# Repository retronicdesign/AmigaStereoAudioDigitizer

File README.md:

# Amiga Stereo Audio Digitizer v1.3b
An Amiga Stereo Digitizer for Audio. Compatible with most softwares. Input gain is adjustable.

## Schematic

## Theory of Operation
This board can convert one or two audio channel to uncompressed digital 8-bit audio stream.  
It connects to the Amiga Parallel Port through a D-SUB-25 male connector. 
It was sucessfully tested with Audio Master IV at a maximum rate of 53KSPS (mono) on an unmodified Amiga 500.

Audio processing on the board is as follow:

1. Audio is preamplified to +5v p-p and biased at +2.5v
2. Left and right channels are multiplexed and sampled alternatively
3. Audio signal is converted to 8-bit using an high-speed ADC

Parallel port signals used to control the process are:
- /STROBE: Amiga ask for the next sample 
- /SELECT: Select the current channel for sample (0=Left, 1= Right)
## PCB

## Bill of materials
| Reference | Quantity | Value | Component | Description | Vendor |
| --- | --- | --- | --- | --- | --- |
| C1, C2, C3,  | 3 | 10uF 10v 10% | Electrolytic, Radial |
| C4, C5, C6,  | 3 | 100nF 50v 10% | Ceramic |
| C7,  | 1 | 47uF 10v 10% | Electrolytic, Radial |
| J1,  | 1 |  | SJ1-3525NG-PI | Stereo jack female connector, Red | Same Sky |
| J2,  | 1 |  | DB25-SL-24 | PCB D-SUB 25 male, Right-Angle | Adam Tech |
| R1, R2, R3, R4,  | 4 | 1K 1% 1/4 Watts | Resistor | Trough hole resistor |
| RV1,  | 1 | A10K | RK09K1110A0J |  Single right-angle potentiometer, 10K Exponential | ALPS |
| U1,  | 1 | | MCP6002 | 1MHz, Low-Power Op Amp, DIP-8 | Microchip |
| U2,  | 1 | | ADG419BNZ | Single SPDT CMOS Analog Switch, DIP-8 | Analog Devices |
| U3,  | 1 | | ADC0820CCN+ | Analog to Digital 8 bits converter, DIP-20 | National Semiconductors |
## Revision information
- 1.0 Original release
- 1.1 Modified D-Sub 25M connector footprint
- 1.2 Modified RCA connector footprint
- 1.3 Redesigned bias for more stable reference and simplified op-amp circuitry + PCB redesign
- 1.3a Corrected routing from v1.3 (issue#2) + replaced SPDT Analog Switch for new part
- 1.3b Corrected routing from v1.3a (issue#3) + replaced RCA plugs for Stereo jack 3.5mm

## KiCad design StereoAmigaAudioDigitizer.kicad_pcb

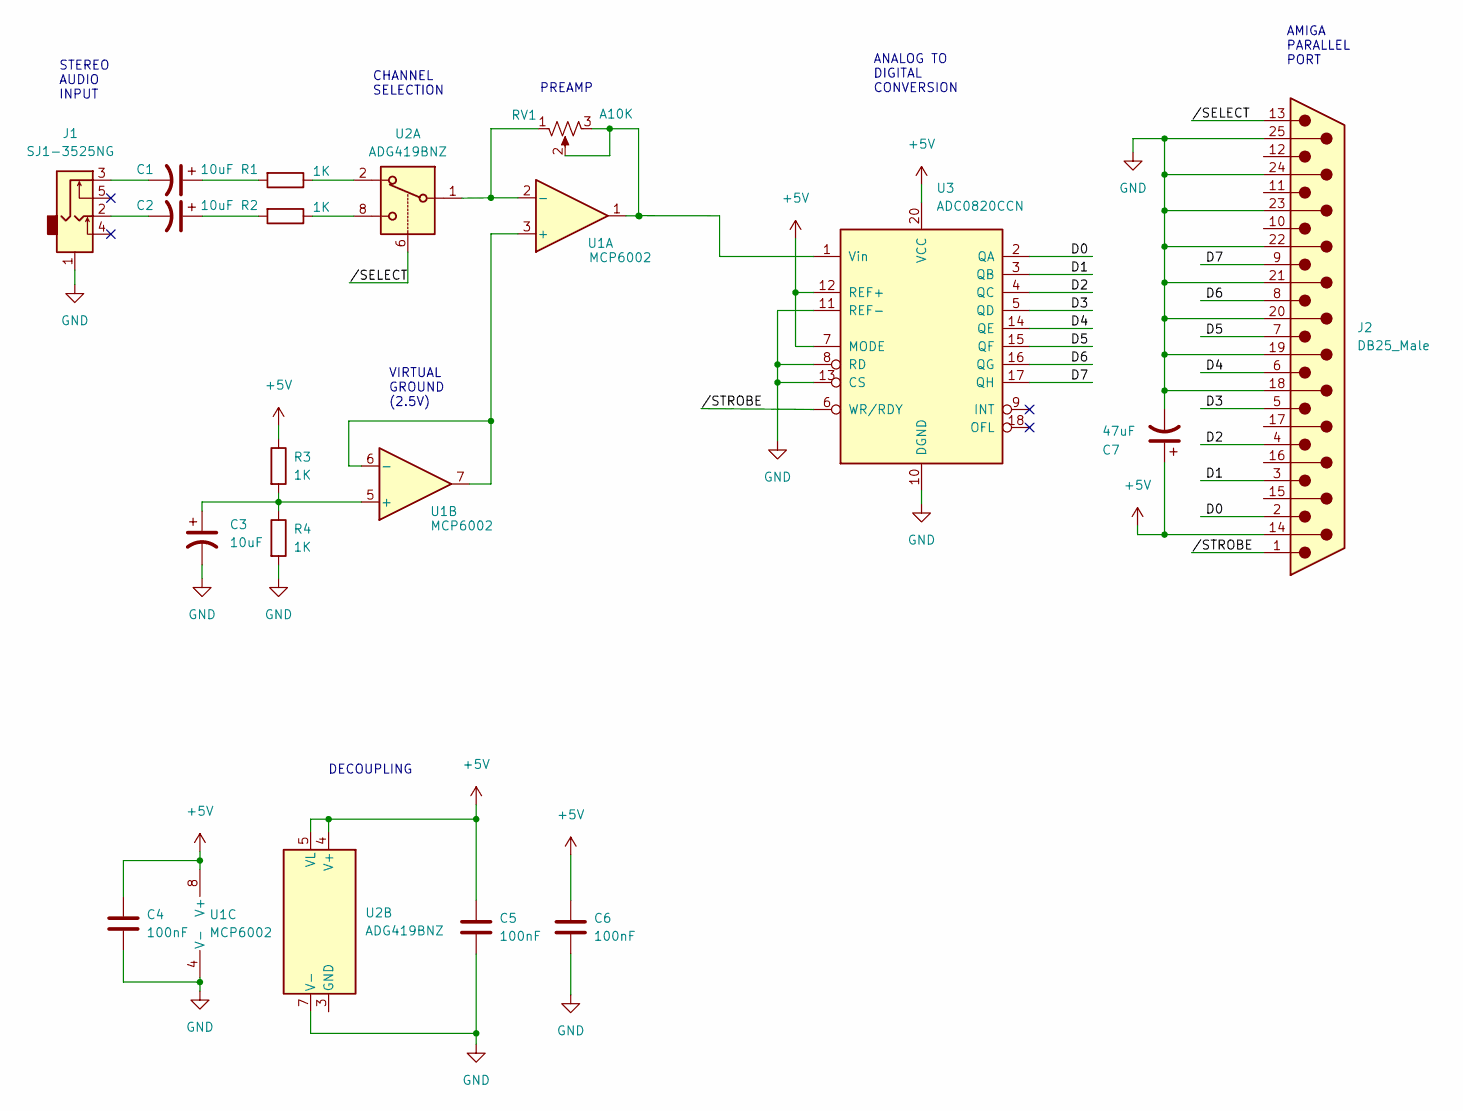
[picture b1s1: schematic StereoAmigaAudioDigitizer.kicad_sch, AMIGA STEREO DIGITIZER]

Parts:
C1, C2, C3: 10uF; CP_Radial_D4.0mm_P1.50mm
C4, C5, C6: 100nF; C_Disc_D3.8mm_W2.6mm_P2.50mm
C7: 47uF; CP_Radial_D4.0mm_P1.50mm
J1: SJ1-3525NG; Jack_3.5mm_CUI_SJ1-3525N_Horizontal_numbers
J2: DB25_Male; DSUB-25_Male_Horizontal_P2.77x2.84mm_EdgePinOffset7.70mm_Ho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
R1, R2, R3, R4: 1K; R_Axial_DIN0204_L3.6mm_D1.6mm_P7.62mm_Horizontal
RV1: A10K; Potentiometer_Alps_RK09K_Single_Horizontal
U1: MCP6002; DIP-8_W7.62mm
U2: ADG419BNZ; DIP-8_W7.62mm
U3: ADC0820CCN; DIP-20_W7.62mm

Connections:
+5V: C4.1, C5.1, C6.1, C7.1, J2.14, R3.1, U1.8 (V+), U2.4 (V+), U2.5 (VL), U3.7 (MODE), U3.12 (REF+), U3.20 (VCC)
/D0: J2.2, U3.2 (QA)
/D1: J2.3, U3.3 (QB)
/D2: J2.4, U3.4 (QC)
/D3: J2.5, U3.5 (QD)
/D4: J2.6, U3.14 (QE)
/D5: J2.7, U3.15 (QF)
/D6: J2.8, U3.16 (QG)
/D7: J2.9, U3.17 (QH)
//SELECT: J2.13, U2.6
//STROBE: J2.1, U3.6 (WR/RDY)
GND: C3.2, C4.2, C5.2, C6.2, C7.2, J1.1, J2.0, J2.18, J2.19, J2.20, J2.21, J2.22, J2.23, J2.24, J2.25, R4.2, RV1.MP, U1.4 (V-), U2.7 (V-), U3.8 (RD), U3.10 (DGND), U3.11 (REF-), U3.13 (CS)
unnamed: C1.1, R1.2
unnamed: C1.2, J1.3
unnamed: C2.1, R2.2
unnamed: C2.2, J1.2
unnamed: C3.1, R3.2, R4.1, U1.5 (+)
unnamed: R1.1, U2.2
unnamed: R2.1, U2.8
unnamed: RV1.1, U1.2 (-), U2.1
unnamed: U1.3 (+), U1.6 (-), U1.7

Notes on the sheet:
DECOUPLING
ANALOG TO DIGITAL CONVERSION
PREAMP
CHANNEL SELECTION
VIRTUAL GROUND (2.5V)
STEREO AUDIO INPUT
AMIGA PARALLEL PORT

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
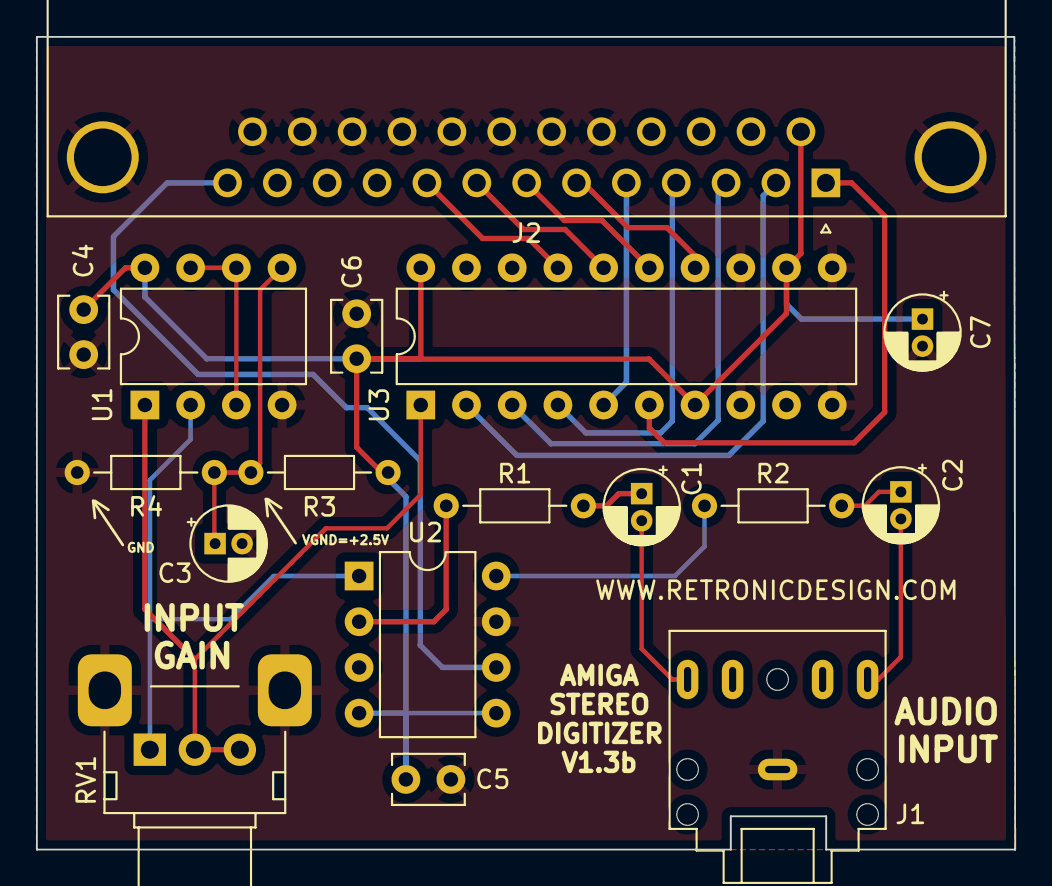
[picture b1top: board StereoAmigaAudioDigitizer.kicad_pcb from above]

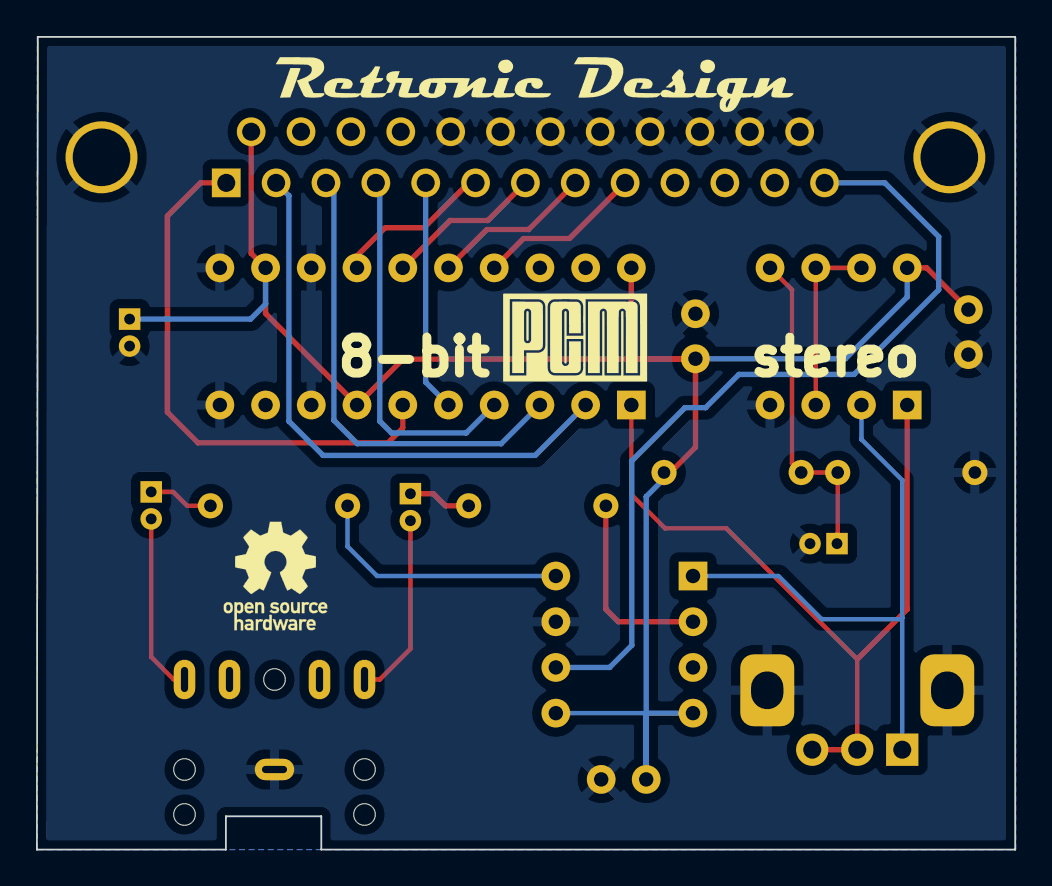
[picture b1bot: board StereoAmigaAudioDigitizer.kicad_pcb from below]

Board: 2 copper layers, 54.4 x 45.2 mm, 20 parts (3 on the bottom side), 22 nets.

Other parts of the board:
LOGO1: OSHW-Logo_5.7x6mm_Copper
LOGO2: LOGO; pcm
LOGO3: LOGO; RetronicDesign

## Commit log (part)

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2023-09-19 Add files via upload
    Modified PCB

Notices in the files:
StereoAmigaAudioDigitizer.kicad_pcb:
RETRONIC DESIGN / OPEN HARDWARE LICENSE
